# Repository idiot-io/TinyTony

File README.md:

## TinyTony V1.0
words http://idiot.io   
code https://github.com/idiot-io/TinyTony 

#### TOC
* [Usage](#usage)
* [Calibration](#calibration)
* [Firmware](#firmware)
* [Hardware](#hardware)

### Usage 
to run Tony you need follow the connection diagram, and an ir remote for calibration.  **no coding is nessecery**

##### Setup 
* LDRx2 - voltage divider
* LINEAR - fixed side

### Calibration   
the system has an initial guess for calibration,   
but you will need to fine tune it to compensate   
for diffrent material and lighting  

*when discussed in this document, [CH+] means press that key on ir remote* 
 
##### Fine tune  
cover LDR #1       press the [CH+] to set `maxval`    
cover LDR #2       press the [CH-] to set `minval`   
uncover both LDRs  press the [CH] to set  `midval`  

##### Trim  
press [-] and [+] to subtract/add to `trimval` value  
  > after fine-tune you will have to trim the motor middle point  
  > press until the motor doesn't turn or twitch in uncovered state.  
  > usually no more then -/+10 is needed.   
  
##### Store  
to put your settings in deep memory press the [200+] key  
  > the setting you provide will be stored in TinyTony   
  > so they are remembered and will  reboot.  
  
##### Info
if DEBUG is on you can use the [EQ] button to watch your settings
you will need a serial RX line connected to pin6 (TX)

##### Sensitivity 
  [PREV] AND [NEXT] keys set the minimal motion threshold 

### Firmware

###### Re-flashing
to upload new firmware you will need
* arduino software runing on your machine and able to communicate with usb
* a programmer (it can be an arduino uno borad, or aspusb programmer)
* an SPI cable to connect tony to the programmer.

##### Libs
most of the libraries are included and referanced from the firmware folder.

[ATTinyCore](https://github.com/SpenceKonde/ATTinyCore)  
EEPROM -used supplied one.   
[sofServo](http://playground.arduino.cc/ComponentLib/Servo)  
[SendOnlySoftwareSerial](https://forum.arduino.cc/index.php?topic=112013.msg841582#msg841582)  
[tiny_ir](https://gist.github.com/SeeJayDee/caa9b5cc29246df44e45b8e7d1b1cdc5) , and [ir_methods](https://github.com/z3t0/Arduino-IRremote/wiki/Receiving-with-the-IRremote-library)  

### Hardware
check the PDF folder in this git to get datasheetsfor parts

#### pinout of ATtiny85  
```
RST    -1+----+8-   VCC  
3/LDR  -2|    |7-   2/PWM  
4/IR   -3|    |6-   1/SERIAL  
GND    -4+----+5-   0/SERVO  
```
[attiny85 pinout complete](https://camo.githubusercontent.com/081b569122da2244ff7de8bae15eb56947d05cc8/687474703a2f2f6472617a7a792e636f6d2f652f696d672f50696e6f7574543835612e6a7067  )

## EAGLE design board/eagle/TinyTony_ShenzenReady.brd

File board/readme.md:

using [svg2shenzen](https://github.com/badgeek/svg2shenzhen) inkscape extension to gerberize the board. 

you can also run following python script ([gist](https://gist.github.com/5shekel/b8e1c65e3923aa3288bfc83cc8a057c2)) after the export to bypass the kicad interface experinace

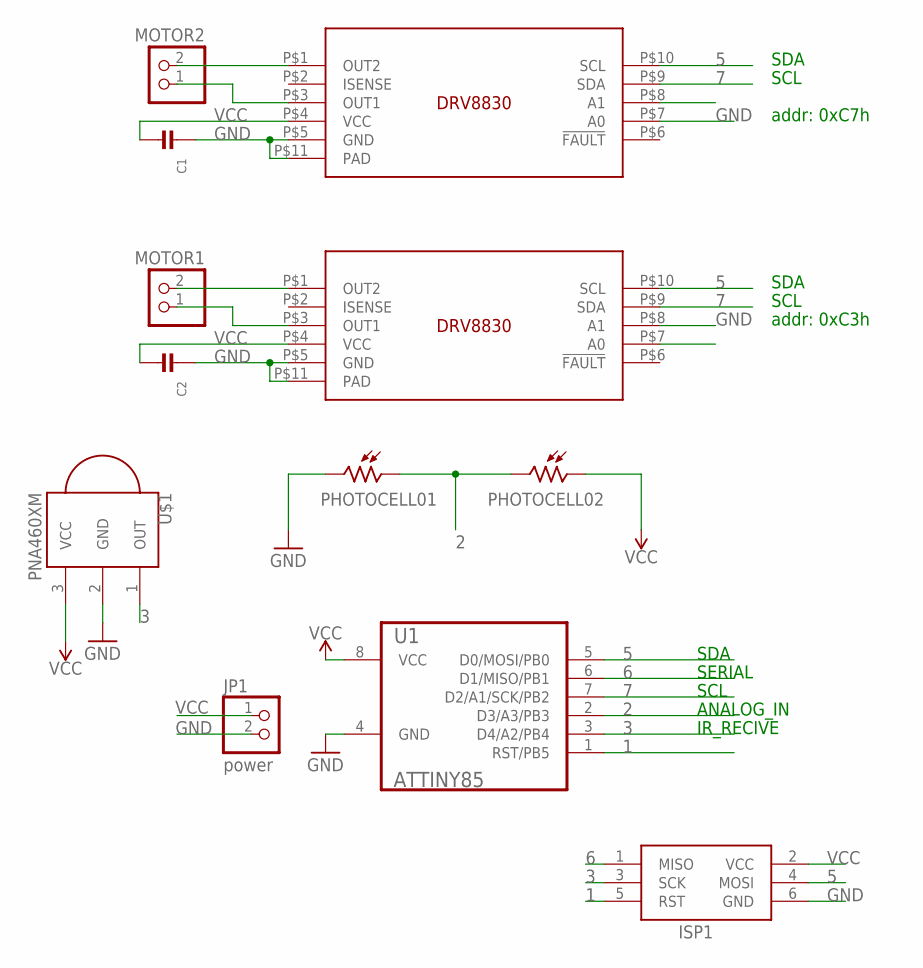
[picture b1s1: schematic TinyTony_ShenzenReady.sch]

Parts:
C1, C2: CAP_CERAMIC1206; 1206
ISP1: AVRISPPOGO; AVRISP-50MIL
JP1: power; 1X02_ROUND
JP2: MOTOR1; 1X02_ROUND
JP3: MOTOR2; 1X02_ROUND
PHOTOCELL01, PHOTOCELL02: PHOTOCELL0N1; TO46-VT200
U1: ATTINY85; SOIC127P798X216-8N
U$1: PNA460XM
U$2, U$3: DRV8830

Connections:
1: ISP1.5 (RST), U1.1 (RST/PB5)
2: PHOTOCELL01.1, PHOTOCELL02.2, U1.2 (D3/A3/PB3)
3: ISP1.3 (SCK), U1.3 (D4/A2/PB4), U$1.1 (OUT)
5: ISP1.4 (MOSI), U1.5 (D0/MOSI/PB0), U$2.P$10 (SCL), U$3.P$10 (SCL)
6: ISP1.1 (MISO), U1.6 (D1/MISO/PB1)
7: U1.7 (D2/A1/SCK/PB2), U$2.P$9 (SDA), U$3.P$9 (SDA)
GND: C1.1, C2.1, ISP1.6 (GND), JP1.2, PHOTOCELL01.2, U1.4 (GND), U$1.2 (GND), U$2.P$5 (GND), U$2.P$8 (A1), U$2.P$11 (PAD), U$3.P$5 (GND), U$3.P$7 (A0), U$3.P$11 (PAD)
unnamed: JP3.1, U$3.P$3 (OUT1)
unnamed: JP2.1, U$2.P$3 (OUT1)
unnamed: JP2.2, U$2.P$1 (OUT2)
unnamed: JP3.2, U$3.P$1 (OUT2)
VCC: C1.2, C2.2, ISP1.2 (VCC), JP1.1, PHOTOCELL02.1, U1.8 (VCC), U$1.3 (VCC), U$2.P$4 (VCC), U$3.P$4 (VCC)

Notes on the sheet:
SDA
SCL
SERIAL
ANALOG_IN
IR_RECIVE
addr: 0xC3h
addr: 0xC7h

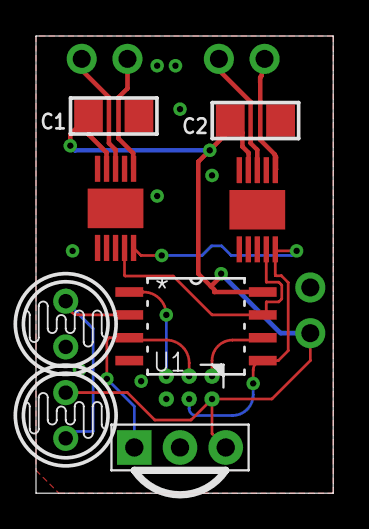
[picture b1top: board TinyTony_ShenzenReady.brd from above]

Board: 2 copper layers, 16.5 x 25.4 mm, 12 parts (0 on the bottom side), 12 nets.

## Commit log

2018-02-28 uno debug version
2018-02-28 tighter
2018-02-28 asses softSendOnly
2018-02-28 SendOnlySoftwareSerial.h doesnt work with sofrservo on
2018-02-28 new servosoft lib
2018-02-28 both servo and serial
2018-02-28 added sendonlytx
2018-03-01 ir compiles
2018-03-01 calibrated to servo driver KC5188
2018-03-01 IR works
2018-03-01 less log
2018-03-01 ir methods
2018-03-01 debounce it
2018-03-01 compare hex
2018-03-01 trimmer switch for IR
2018-03-04 testing servo motor
2018-03-04 docs
2018-03-04 expl
2018-03-06 debuging, but works
2018-03-06 board schema
2018-03-06 pdf board schema
2018-03-06 slight move
2018-03-06 visual
2018-03-08 board
2018-03-08 smd parts
2018-03-09 li addons
2018-03-15 yet another layout
2018-03-15 2 drivers and cap
2018-03-16 bigger, 1206cp
2018-03-19 Create gfx
2018-03-19 easyEDA svg
2018-03-21 new svg from easyEDA
2018-03-21 new layout
2018-03-22 added holes+few changes
2018-03-31 svg for testing svg2shenzhen, not for use
2018-05-23 work on svg
2018-05-23 gerbes
2018-06-16 tweaks to drill holes, drv pdf
2018-06-16 pre setup for replacing drv8830 foortprint
2018-06-17 looks ok
2018-06-17 adde res smd footprints
2018-06-17 added isnese and bypasscap
2018-06-17 mask tweaks and zipped gerber
2018-06-26 made a panel with panelizer, sent to fab
2018-07-10 removerd old boards
2018-07-10 add fritizng layout
2018-07-11 breadboard layout
2018-07-11 slim test code
2018-07-13 added eagle schema and design
2018-07-14 tinyDRV8330 test code
2018-07-14 tinyDRV8330 test code 2
2018-07-29 changed wprogram to aruino.h
2018-12-20 firmware: vscode
2018-12-20 vsdoce/
2018-12-20 both same dir, works
2018-12-23 twidle

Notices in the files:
parts and their libraries:
SparkFun-PowerSymbols: Licensing: Creative Commons ShareAlike 4.0 International - https://creativecommons.org/licenses/by-sa/4.0
